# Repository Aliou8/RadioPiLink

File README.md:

# RadioPiLink

RadioPiLink est un projet IoT permettant la transmission de données radio depuis un microcontrôleur STM32WLE5 vers un Raspberry Pi, puis leur relais sur un réseau local pour traitement et visualisation.

## Table des matières
- [Fonctionnalités](#fonctionnalités)
- [Architecture](#architecture)
- [Licence](#licence)

## Fonctionnalités
- Réception radio sur STM32WLE5
- Passerelle vers Raspberry Pi
- Routage des données vers le réseau local
- Points d'extension pour traitement et visualisation

## Architecture

Consultez :
* [meta-radiopilink](meta-radiopilink/README.md)
* [hardware](hardware/README.md)
* [software](software/README.md)

## Licence
Ce projet est distribué sous la licence GNU GPL v3. Voir le fichier LICENSE pour les détails.

## Contact
Pour toute question ou contribution, ouvrez une issue ou contactez les mainteneurs via la page du dépôt.

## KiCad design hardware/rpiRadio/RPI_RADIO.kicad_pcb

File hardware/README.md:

La carte est basée sur un STM32WLE5CCU6 dont la particularité est d'embarquer directement un module sub‑radio.

* Radio
    * **Plage de fréquence :** 150 MHz à 960 MHz
    * **Modulation :** LoRa®, (G)FSK, (G)MSK et BPSK
    * **Sensibilité RX :** –123 dBm pour 2-FSK (à 1,2 Kbit/s), –148 dBm pour LoRa® (à 10,4 kHz, facteur d'étalement 12)
    * **Puissance de sortie élevée du transmetteur :** programmable jusqu'à +22 dBm
    * **Puissance de sortie faible du transmetteur :** programmable jusqu'à +15 dBm

Le design actuel ne fonctionne qu'avec des fréquences et des puissances élevées, mais les versions suivantes permettront de mettre en place des commutateurs RF et des commutateurs d'alimentation pour choisir entre **HP/LP** et **HF/LF**.

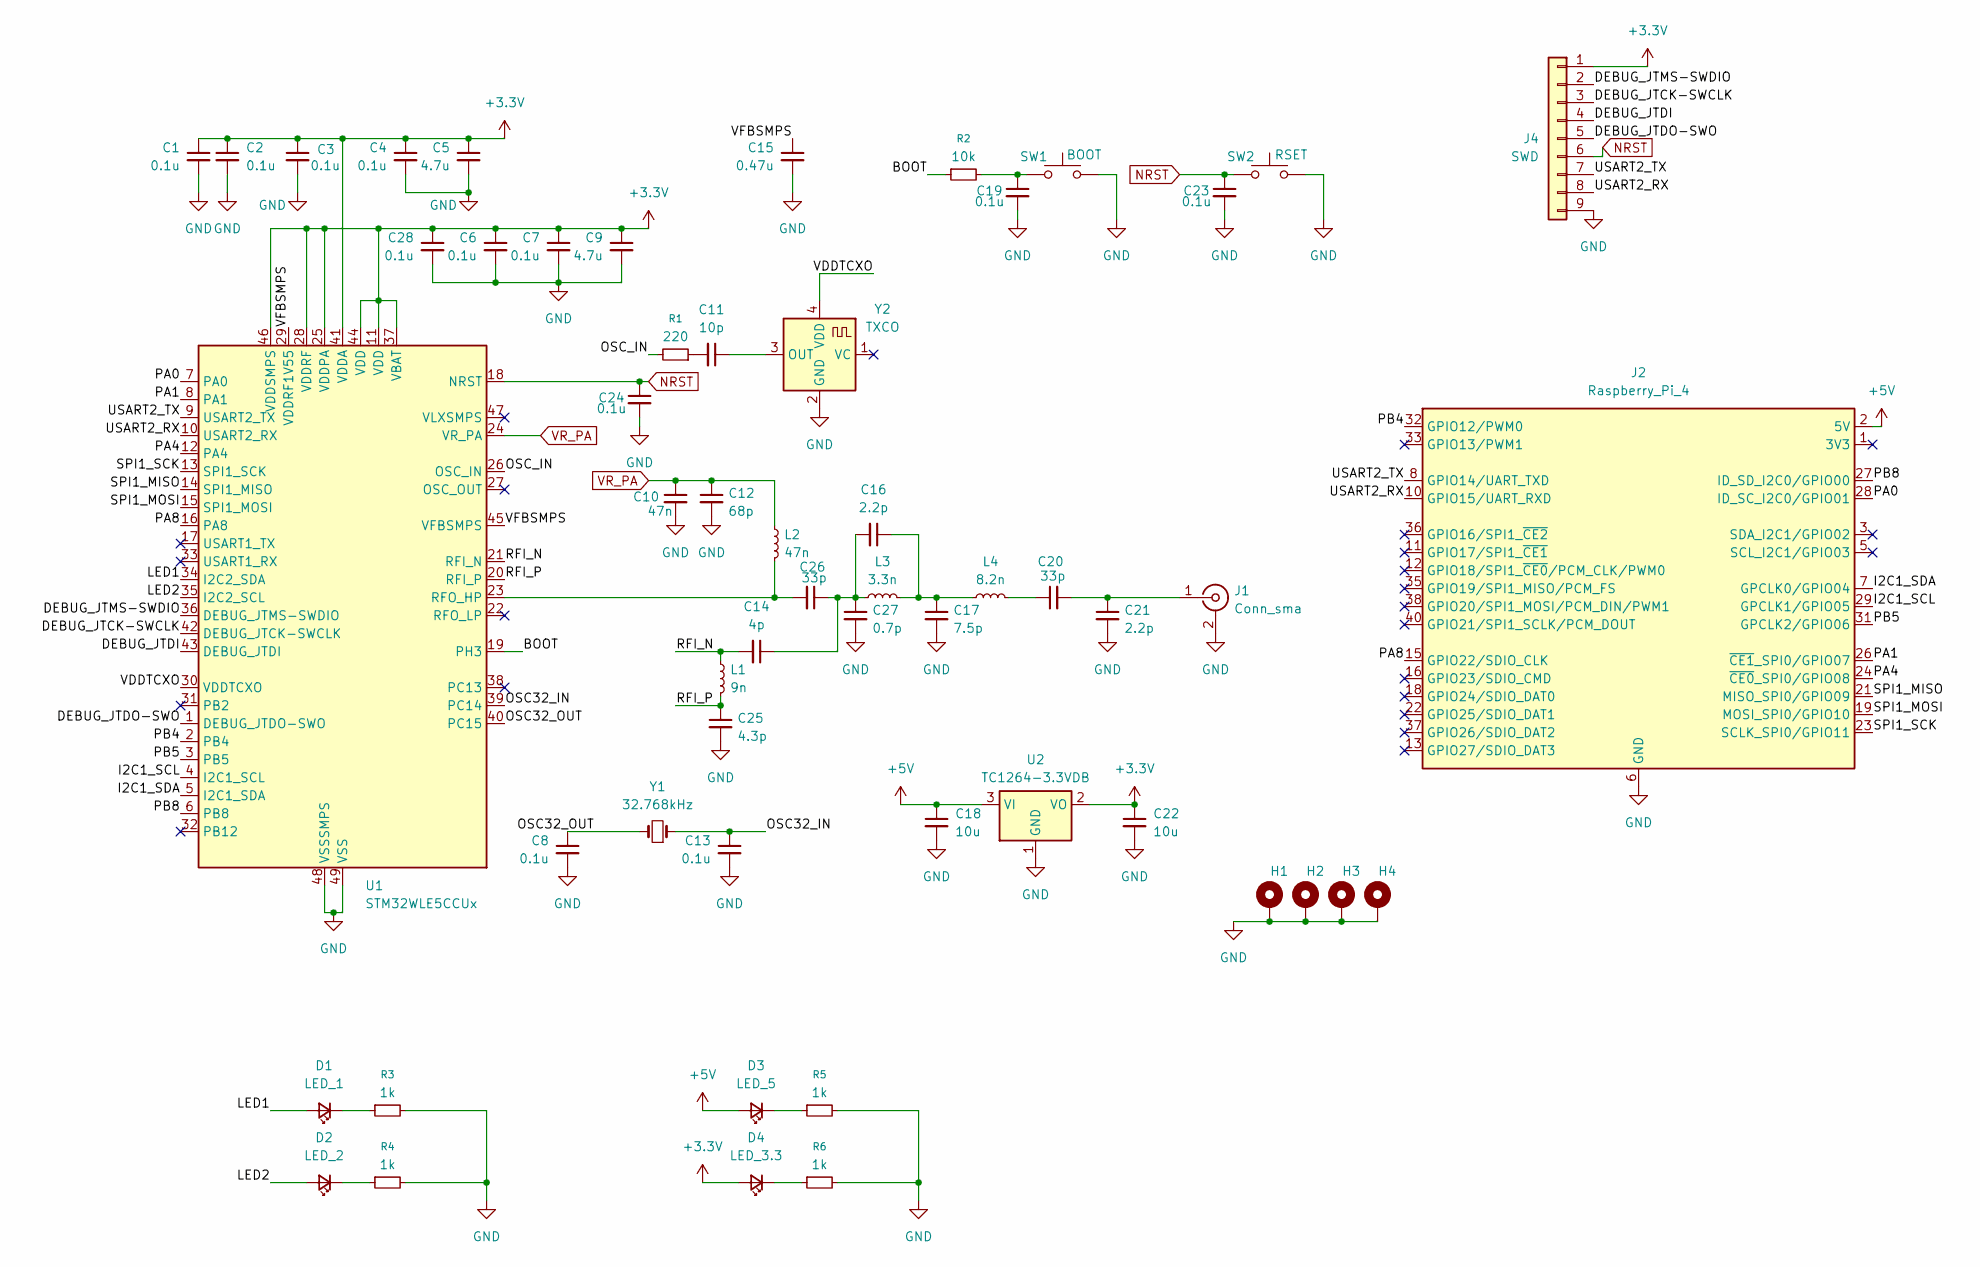
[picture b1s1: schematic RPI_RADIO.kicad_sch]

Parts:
C1, C2, C3, C4, C6, C7, C8, C13, C19, C23, C24, C28: 0.1u; C_0603_1608Metric
C5, C9: 4.7u; C_0603_1608Metric
C10: 47n; C_0603_1608Metric
C11: 10p; C_0603_1608Metric
C12: 68p; C_0603_1608Metric
C14: 4p; C_0603_1608Metric
C15: 0.47u; C_0603_1608Metric
C16, C21: 2.2p; C_0603_1608Metric
C17: 7.5p; C_0603_1608Metric
C18, C22: 10u; C_0805_2012Metric
C20, C26: 33p; C_0603_1608Metric
C25: 4.3p; C_0603_1608Metric
C27: 0.7p; C_0603_1608Metric
D1: LED_1; LED_0603_1608Metric
D2: LED_2; LED_0603_1608Metric
D3: LED_5; LED_0603_1608Metric
D4: LED_3.3; LED_0603_1608Metric
H1, H2, H3, H4: MountingHole_Pad; MountingHole_2.5mm_Pad
J1: Conn_sma; SMA_Amphenol_132289_EdgeMount
J2: Raspberry_Pi_4; PinSocket_2x20_P2.54mm_Vertical
J4: SWD; PinHeader_1x09_P2.54mm_Vertical
L1: 9n; L_0402_1005Metric
L2: 47n; L_0603_1608Metric
L3: 3.3n; L_0603_1608Metric
L4: 8.2n; L_0603_1608Metric
R1: 220; R_0603_1608Metric
R2: 10k; R_0603_1608Metric
R3, R4, R5, R6: 1k; R_0603_1608Metric
SW1: BOOT; SW_Push_1P1T_NO_CK_KMR2
SW2: RSET; SW_Push_1P1T_NO_CK_KMR2
U1: STM32WLE5CCUx; QFN-48-1EP_7x7mm_P0.5mm_EP5.6x5.6mm
U2: TC1264-3.3VDB; SOT-223-3_TabPin2
Y1: 32.768kHz; Crystal_SMD_3215-2Pin_3.2x1.5mm
Y2: TXCO; Oscillator_SMD_SeikoEpson_SG8002CE-4Pin_3.2x2.5mm

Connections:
+3.3V: C1.1, C2.1, C3.1, C4.1, C5.1, C6.1, C7.1, C9.1, C22.1, C28.1, D4.2 (A), J4.1, U1.11 (VDD), U1.25 (VDDPA), U1.28 (VDDRF), U1.37 (VBAT), U1.41 (VDDA), U1.44 (VDD), U1.46 (VDDSMPS), U2.2 (VO)
+5V: C18.1, D3.2 (A), J2.2 (5V), J2.4 (5V), U2.3 (VI)
/BOOT: R2.1, U1.19 (PH3)
/DEBUG_JTCK-SWCLK: J4.3, U1.42 (DEBUG_JTCK-SWCLK)
/DEBUG_JTDI: J4.4, U1.43 (DEBUG_JTDI)
/DEBUG_JTDO-SWO: J4.5, U1.1 (DEBUG_JTDO-SWO)
/DEBUG_JTMS-SWDIO: J4.2, U1.36 (DEBUG_JTMS-SWDIO)
/I2C1_SCL: J2.29 (GPCLK1/GPIO05), U1.4 (I2C1_SCL)
/I2C1_SDA: J2.7 (GPCLK0/GPIO04), U1.5 (I2C1_SDA)
/LED1: D1.2 (A), U1.34 (I2C2_SDA)
/LED2: D2.2 (A), U1.35 (I2C2_SCL)
/OSC32_IN: C13.1, U1.39 (PC14), Y1.1
/OSC32_OUT: C8.1, U1.40 (PC15), Y1.2
/OSC_IN: R1.2, U1.26 (OSC_IN)
/PA0: J2.28 (ID_SC_I2C0/GPIO01), U1.7 (PA0)
/PA1: J2.26 (~CE1_SPI0/GPIO07), U1.8 (PA1)
/PA4: J2.24 (~CE0_SPI0/GPIO08), U1.12 (PA4)
/PA8: J2.15 (GPIO22/SDIO_CLK), U1.16 (PA8)
/PB4: J2.32 (GPIO12/PWM0), U1.2 (PB4)
/PB5: J2.31 (GPCLK2/GPIO06), U1.3 (PB5)
/PB8: J2.27 (ID_SD_I2C0/GPIO00), U1.6 (PB8)
/RFI_N: C14.2, L1.1, U1.21 (RFI_N)
/RFI_P: C25.1, L1.2, U1.20 (RFI_P)
/SPI1_MISO: J2.21 (MISO_SPI0/GPIO09), U1.14 (SPI1_MISO)
/SPI1_MOSI: J2.19 (MOSI_SPI0/GPIO10), U1.15 (SPI1_MOSI)
/SPI1_SCK: J2.23 (SCLK_SPI0/GPIO11), U1.13 (SPI1_SCK)
/USART2_RX: J2.10 (GPIO15/UART_RXD), J4.8, U1.10 (USART2_RX)
/USART2_TX: J2.8 (GPIO14/UART_TXD), J4.7, U1.9 (USART2_TX)
/VDDTCXO: U1.30 (VDDTCXO), Y2.4 (VDD)
/VFBSMPS: C15.1, U1.29 (VDDRF1V55), U1.45 (VFBSMPS)
GND: C1.2, C2.2, C3.2, C4.2, C5.2, C6.2, C7.2, C8.2, C9.2, C10.2, C12.2, C13.2, C15.2, C17.2, C18.2, C19.2, C21.2, C22.2, C23.2, C24.2, C25.2, C27.2, C28.2, H1.1, H2.1, H3.1, H4.1, J1.2 (Ext), J2.6 (GND), J2.9 (GND), J2.14 (GND), J2.20 (GND), J2.25 (GND), J2.30 (GND), J2.34 (GND), J2.39 (GND), J4.9, R3.2, R4.2, R5.2, R6.2, SW1.2, SW2.2, U1.48 (VSSSMPS), U1.49 (VSS), U2.1 (GND), Y2.2 (GND)
NRST: C23.1, C24.1, J4.6, SW2.1, U1.18 (NRST)
unnamed: C11.2, R1.1
unnamed: C14.1, C16.2, C26.1, C27.1, L3.1
unnamed: C16.1, C17.1, L3.2, L4.1
unnamed: C19.1, R2.2, SW1.1
unnamed: C20.1, L4.2
unnamed: D1.1 (K), R3.1
unnamed: D2.1 (K), R4.1
unnamed: D3.1 (K), R5.1
unnamed: D4.1 (K), R6.1
unnamed: C20.2, C21.1, J1.1 (In)
unnamed: C26.2, L2.2, U1.23 (RFO_HP)
unnamed: C11.1, Y2.3 (OUT)
VR_PA: C10.1, C12.1, L2.1, U1.24 (VR_PA)

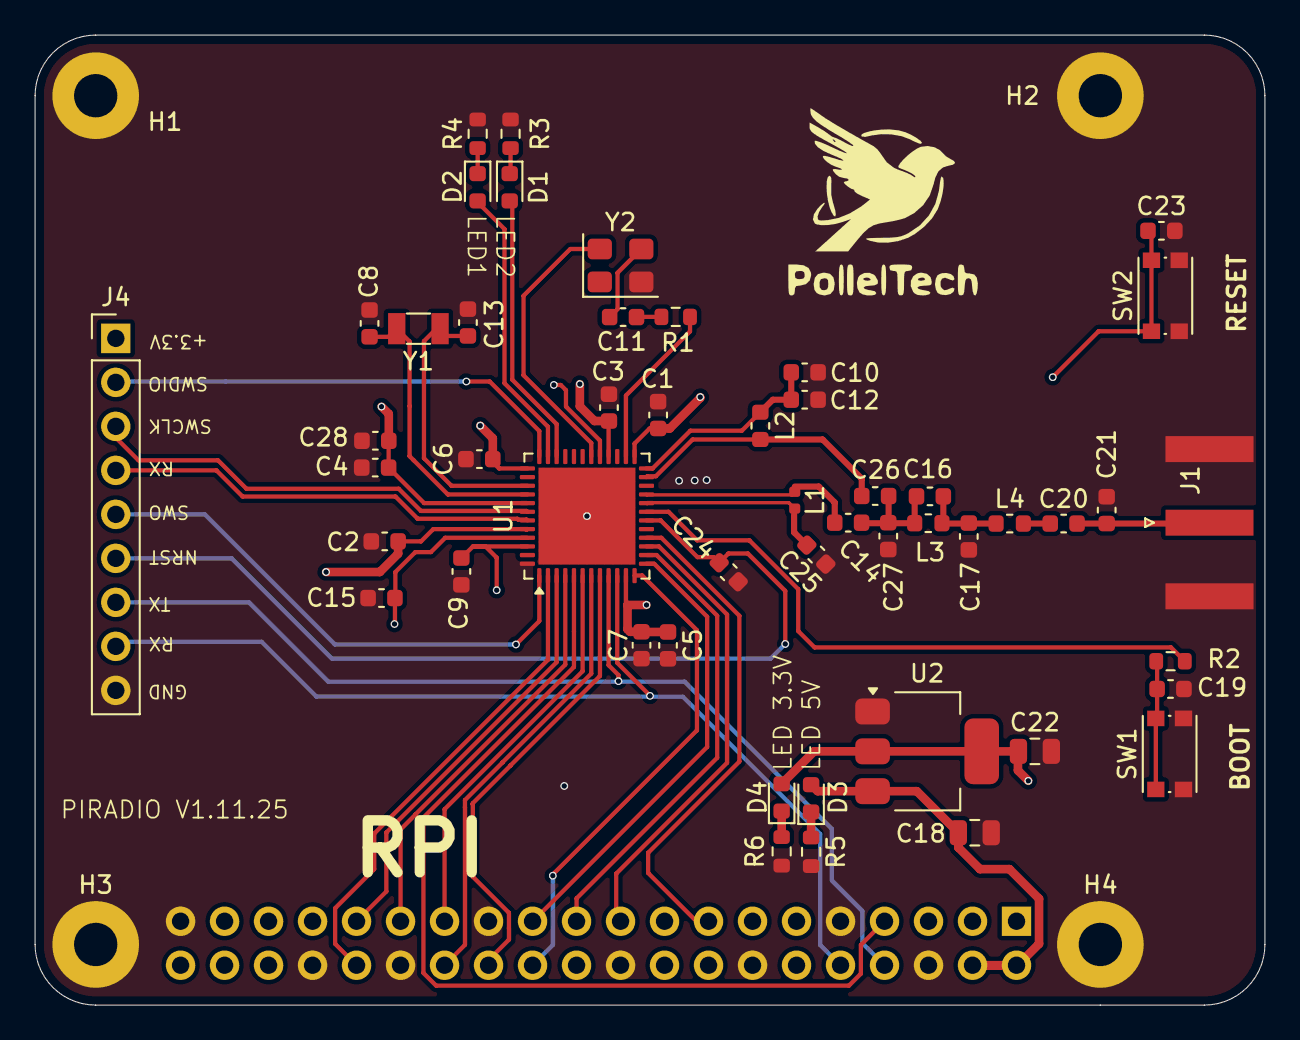
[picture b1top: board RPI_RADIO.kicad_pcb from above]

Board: 4 copper layers, 71.0 x 56.0 mm, 55 parts (1 on the bottom side), 45 nets.

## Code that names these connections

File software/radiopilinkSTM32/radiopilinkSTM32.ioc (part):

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Mcu.Name=STM32WLE5CCUx
Mcu.Package=UFQFPN48
Mcu.UserName=STM32WLE5CCUx
PA0.GPIOParameters=GPIO_Label
PA0.GPIO_Label=PA0
PA0.Signal=GPIO_Output
PA1.GPIOParameters=GPIO_Label
PA1.GPIO_Label=PA1
PA1.Signal=GPIO_Output
PA11.GPIOParameters=GPIO_Label
PA11.GPIO_Label=LED1
PA11.Signal=GPIO_Output
PA12.GPIOParameters=GPIO_Label
PA12.GPIO_Label=LED2
PA12.Signal=GPIO_Output
PA13.Mode=JTAG_4_pins
PA13.Signal=DEBUG_JTMS-SWDIO
PA14.Mode=JTAG_4_pins
PA14.Signal=DEBUG_JTCK-SWCLK
PA15.Mode=JTAG_4_pins
PA15.Signal=DEBUG_JTDI
PA2.Mode=Asynchronous
PA2.Signal=USART2_TX
PA3.Mode=Asynchronous
PA3.Signal=USART2_RX
PA4.GPIOParameters=GPIO_Label
PA4.GPIO_Label=PA4
PA4.Signal=GPIO_Output
PA5.Mode=Full_Duplex_Master
PA5.Signal=SPI1_SCK
PA6.Mode=Full_Duplex_Master
PA6.Signal=SPI1_MISO
PA7.Mode=Full_Duplex_Master
PA7.Signal=SPI1_MOSI
PA8.GPIOParameters=GPIO_Label
PA8.GPIO_Label=PA8
PA8.Signal=GPIO_Analog
PB0-VDD_TCXO.Mode=HSE-TCXO
PB0-VDD_TCXO.Signal=VDDTCXO
PB3.Mode=JTAG_4_pins
PB3.Signal=DEBUG_JTDO-SWO
PB4.GPIOParameters=GPIO_Label
PB4.GPIO_Label=PB4
PB4.Signal=GPIO_Output
PB5.GPIOParameters=GPIO_Label
PB5.GPIO_Label=PB5
PB5.Signal=GPIO_Output
PB6.Mode=I2C
PB6.Signal=I2C1_SCL
PB7.Mode=I2C
PB7.Signal=I2C1_SDA
PB8.GPIOParameters=GPIO_Label
PB8.GPIO_Label=PB8
PB8.Signal=GPIO_Output
PC14-OSC32_IN.Mode=LSE-External-Oscillator
PC14-OSC32_IN.Signal=RCC_OSC32_IN
PC15-OSC32_OUT.Mode=LSE-External-Oscillator
PC15-OSC32_OUT.Signal=RCC_OSC32_OUT
RCC.HSE_VALUE=32000000
RCC.SYSCLKFreq_VALUE=48000000
RCC.SYSCLKSource=RCC_SYSCLKSOURCE_PLLCLK
board=custom

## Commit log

2025-11-29 Add version and license badges to README
    Added badges for version and license to README
2025-11-30 Add meta-radiopilink
2025-12-01 Ajout de hard and pcb
2025-12-01 remove pretty
2025-12-03 Work on yocto 1
2025-12-03 Add layer README
2025-12-03 Config gitignore
2025-12-03 STM32 soft
2025-12-03 Description README
2025-12-03 Fix formatting in hardware README for radio section
    Correct formatting and improve readability of the radio specifications.
2025-12-03 Fix formatting in hardware README
    Correct formatting of modulation and sensitivity details in README.
2025-12-03 Fix formatting in hardware README
2025-12-03 add .md
2025-12-03 Correction des README
2025-12-03 Correction du README de meta-radiopilink
2025-12-09 Avan sur linux yocto 1
2025-12-09 Correction de la commande de construction de l'image RadioPiLink dans le README

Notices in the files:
README.md:
License: GNU GPL v3
